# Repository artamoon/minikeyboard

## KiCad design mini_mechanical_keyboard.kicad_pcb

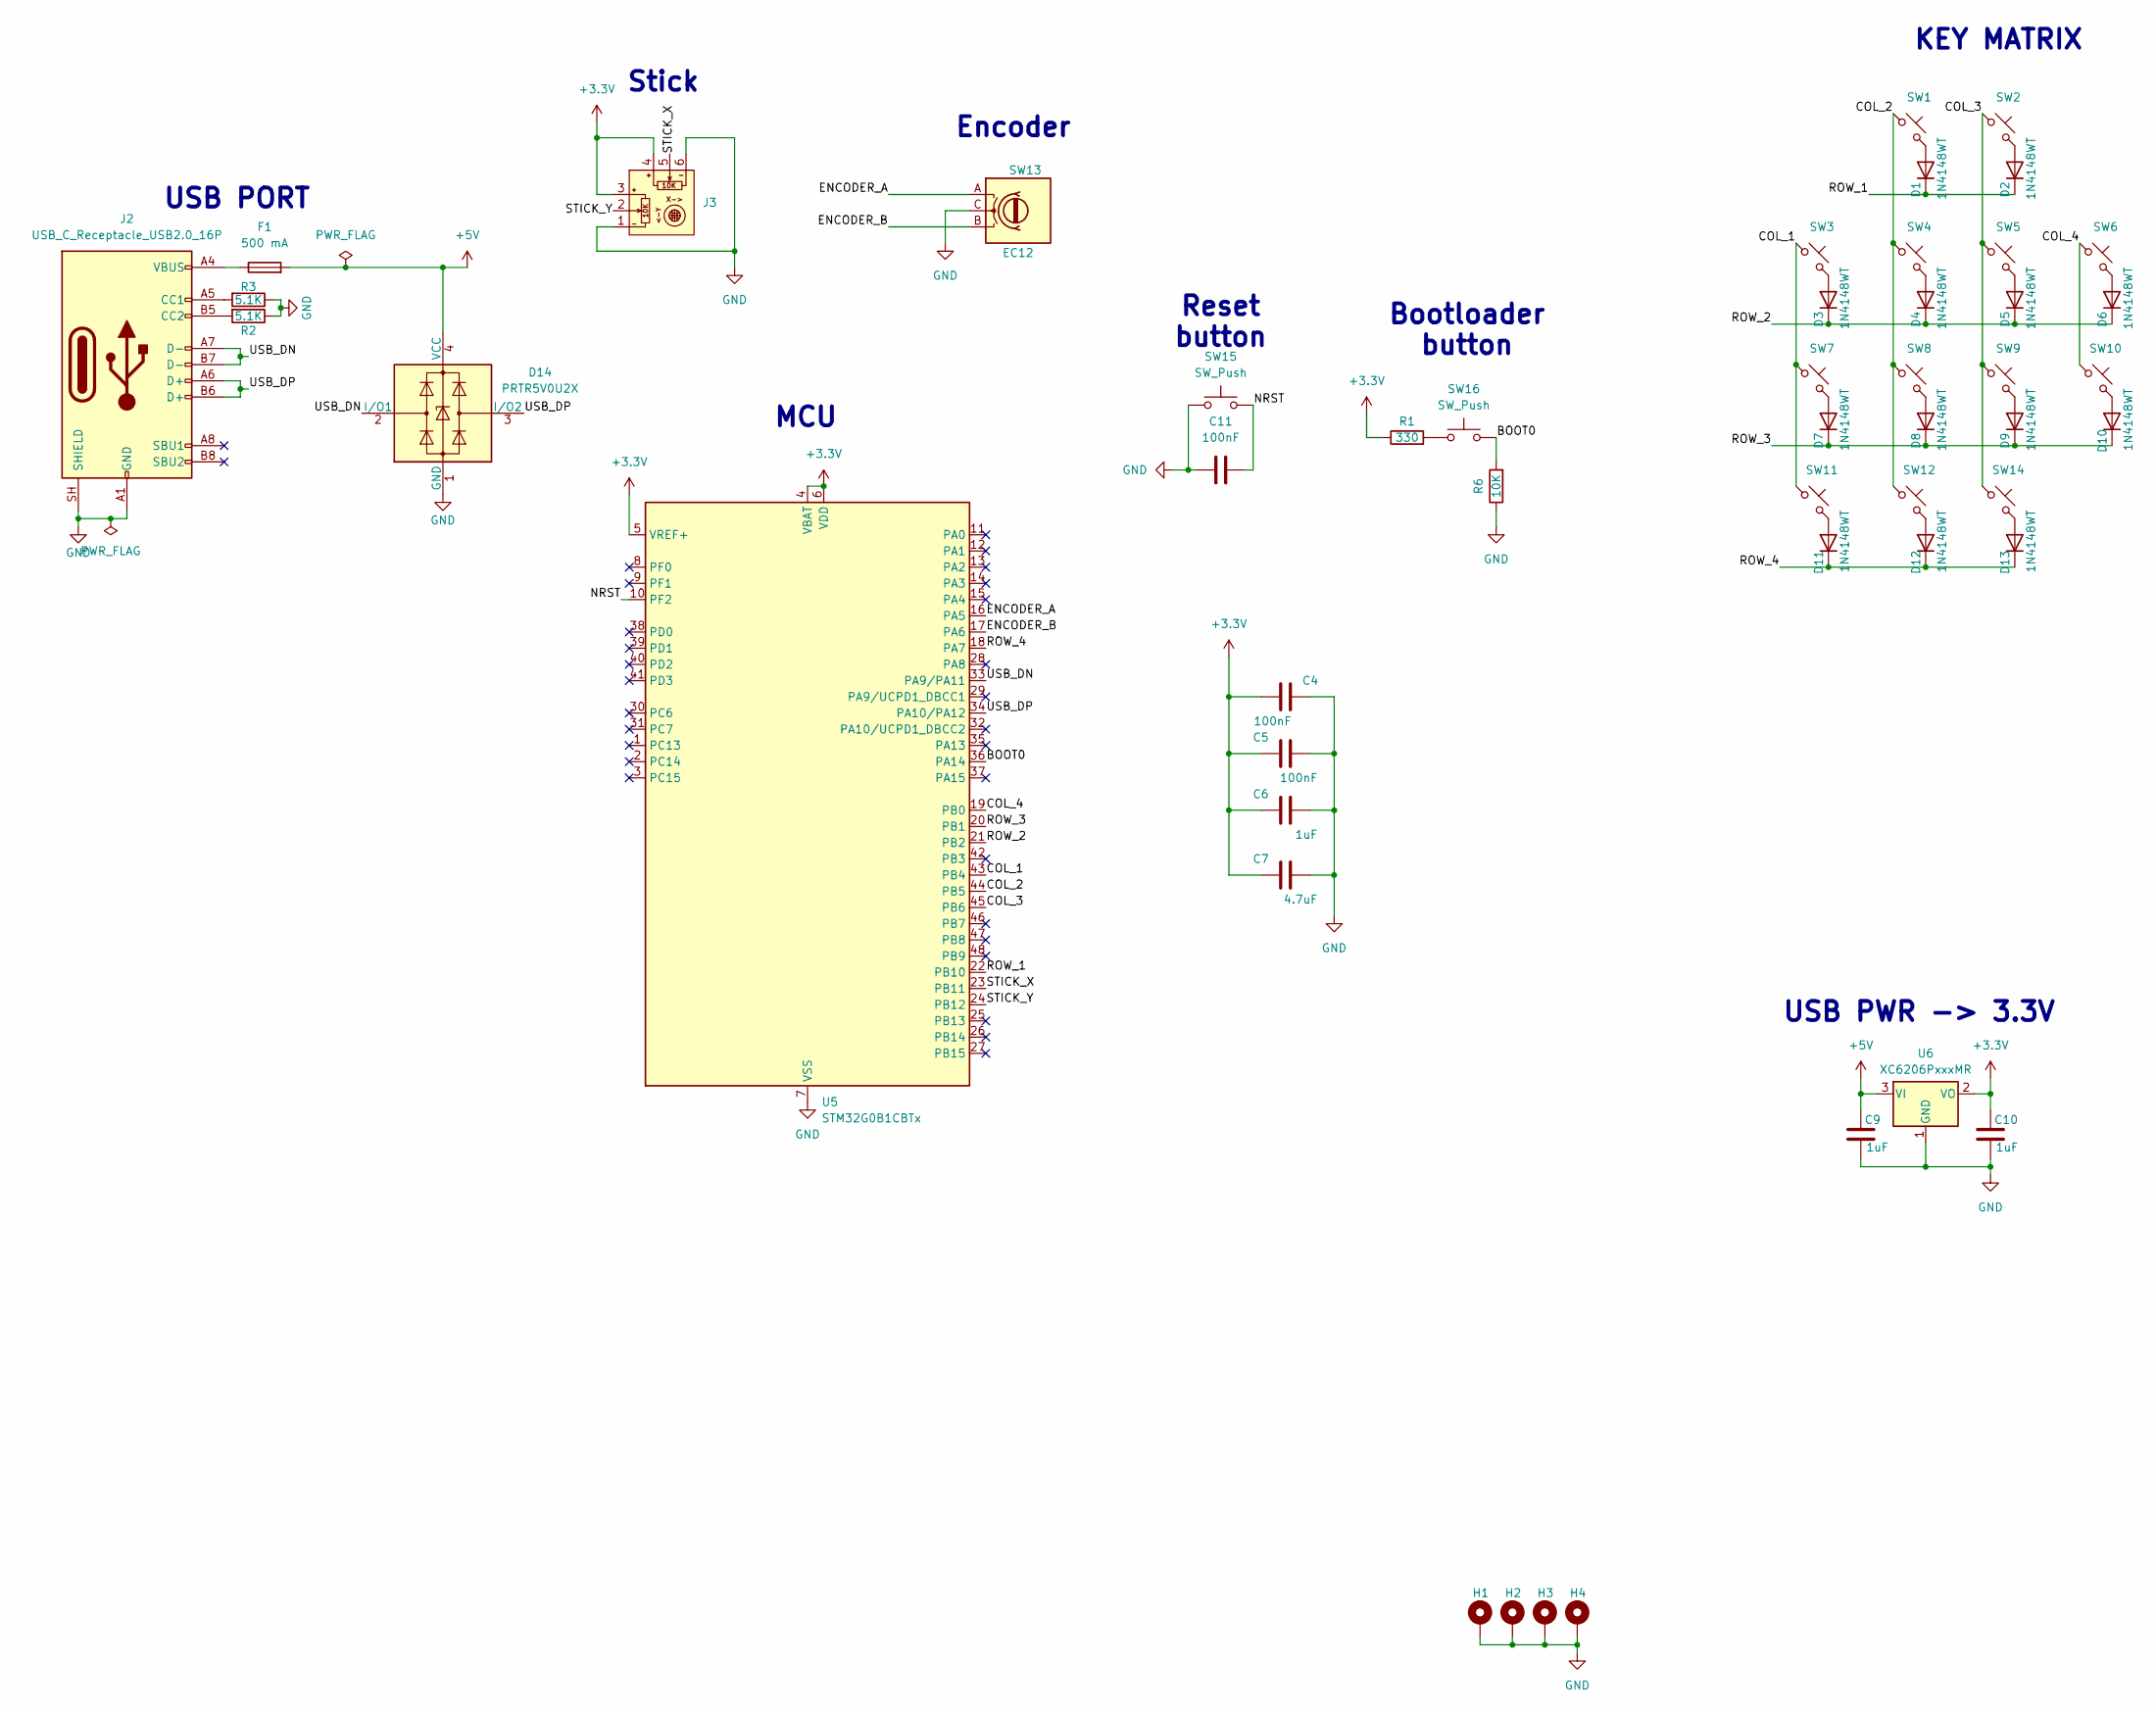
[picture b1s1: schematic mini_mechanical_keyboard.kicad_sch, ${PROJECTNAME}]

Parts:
C4, C5: 100nF; C_0402_1005Metric; LCSC C1525
C6: 1uF; C_0603_1608Metric; LCSC C1525
C7: 4.7uF; C_0805_2012Metric; LCSC C19666
C9, C10: 1uF; C_0603_1608Metric; LCSC C15525
C11: 100nF; C_0402_1005Metric
D1, D2, D3, D4, D5, D6, D7, D8, D9, D10, D11, D12, D13: 1N4148WT; D_SOD-523; LCSC C7420320
D14: PRTR5V0U2X; SOT-143
F1: 500 mA; Fuse_1206_3216Metric_Pad1.42x1.75mm_HandSolder
H1, H2, H3, H4: MountingHole_Pad; MountingHole_2.7mm_Pad_Via
J2: USB_C_Receptacle_USB2.0_16P; USB_C_HRO_TYPE-C-31-M-12
J3: Mini 2-Axis Analog Thumbstick
R1: 330; R_0402_1005Metric
R2, R3: 5.1K; R_0402_1005Metric; LCSC C25905
R6: 10K; R_0402_1005Metric
SW1, SW2, SW3, SW4, SW5, SW6, SW7, SW8, SW9, SW10, SW12, SW14: SW_Push_45deg; SW_choc_v2_HS_CPG135001S30_1u
SW11: SW_Push_45deg; SW_SPST_SKQG_WithStem
SW13: EC12; RotaryEncoder_Alps_EC12E_Vertical_H20mm
SW15, SW16: SW_Push; SW_SPST_TL3305A
U5: STM32G0B1CBTx; LQFP-48_7x7mm_P0.5mm
U6: XC6206PxxxMR; SOT-23-3

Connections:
+3.3V: C4.2, C5.1, C6.1, C7.1, C10.1, J3.3, J3.4, R1.1, U5.4 (VBAT), U5.5 (VREF+), U5.6 (VDD), U6.2 (VO)
+5V: C9.1, D14.4 (VCC), F1.2, U6.3 (VI)
/BOOT0: R6.2, SW16.2, U5.36 (PA14)
/COL_1: SW3.1, SW7.1, SW11.1, U5.43 (PB4)
/COL_2: SW1.1, SW4.1, SW8.1, SW12.1, U5.44 (PB5)
/COL_3: SW2.1, SW5.1, SW9.1, SW14.1, U5.45 (PB6)
/COL_4: SW6.1, SW10.1, U5.19 (PB0)
/ENCODER_A: SW13.A, U5.16 (PA5)
/ENCODER_B: SW13.B, U5.17 (PA6)
/NRST: C11.2, SW15.2, U5.10 (PF2)
/ROW_1: D1.1 (K), D2.1 (K), U5.22 (PB10)
/ROW_2: D3.1 (K), D4.1 (K), D5.1 (K), D6.1 (K), U5.21 (PB2)
/ROW_3: D7.1 (K), D8.1 (K), D9.1 (K), D10.1 (K), U5.20 (PB1)
/ROW_4: D11.1 (K), D12.1 (K), D13.1 (K), U5.18 (PA7)
/STICK_X: J3.5, U5.23 (PB11)
/STICK_Y: J3.2, U5.24 (PB12)
/USB_DN: D14.2 (I/O1), J2.A7 (D-), J2.B7 (D-), U5.33 (PA9/PA11)
/USB_DP: D14.3 (I/O2), J2.A6 (D+), J2.B6 (D+), U5.34 (PA10/PA12)
GND: C4.1, C5.2, C6.2, C7.2, C9.2, C10.2, C11.1, D14.1 (GND), H1.1 (1_1), H2.1 (1_1), H3.1 (1_1), H4.1 (1_1), J2.A1 (GND), J2.A12 (GND), J2.B1 (GND), J2.B12 (GND), J2.SH (SHIELD), J3.1, J3.6, R2.1, R3.1, R6.1, SW13.C, SW15.1, U5.7 (VSS), U6.1 (GND)
unnamed: D1.2 (A), SW1.2
unnamed: D2.2 (A), SW2.2
unnamed: D3.2 (A), SW3.2
unnamed: D4.2 (A), SW4.2
unnamed: D5.2 (A), SW5.2
unnamed: D6.2 (A), SW6.2
unnamed: D7.2 (A), SW7.2
unnamed: D8.2 (A), SW8.2
unnamed: D9.2 (A), SW9.2
unnamed: D10.2 (A), SW10.2
unnamed: D11.2 (A), SW11.2
unnamed: D12.2 (A), SW12.2
unnamed: D13.2 (A), SW14.2
unnamed: F1.1, J2.A4 (VBUS), J2.A9 (VBUS), J2.B4 (VBUS), J2.B9 (VBUS)
unnamed: J2.A5 (CC1), R3.2
unnamed: J2.B5 (CC2), R2.2
unnamed: R1.2, SW16.1

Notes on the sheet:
Encoder
USB PORT
Bootloader button
MCU
Reset button
KEY MATRIX
USB PWR -> 3.3V
Stick

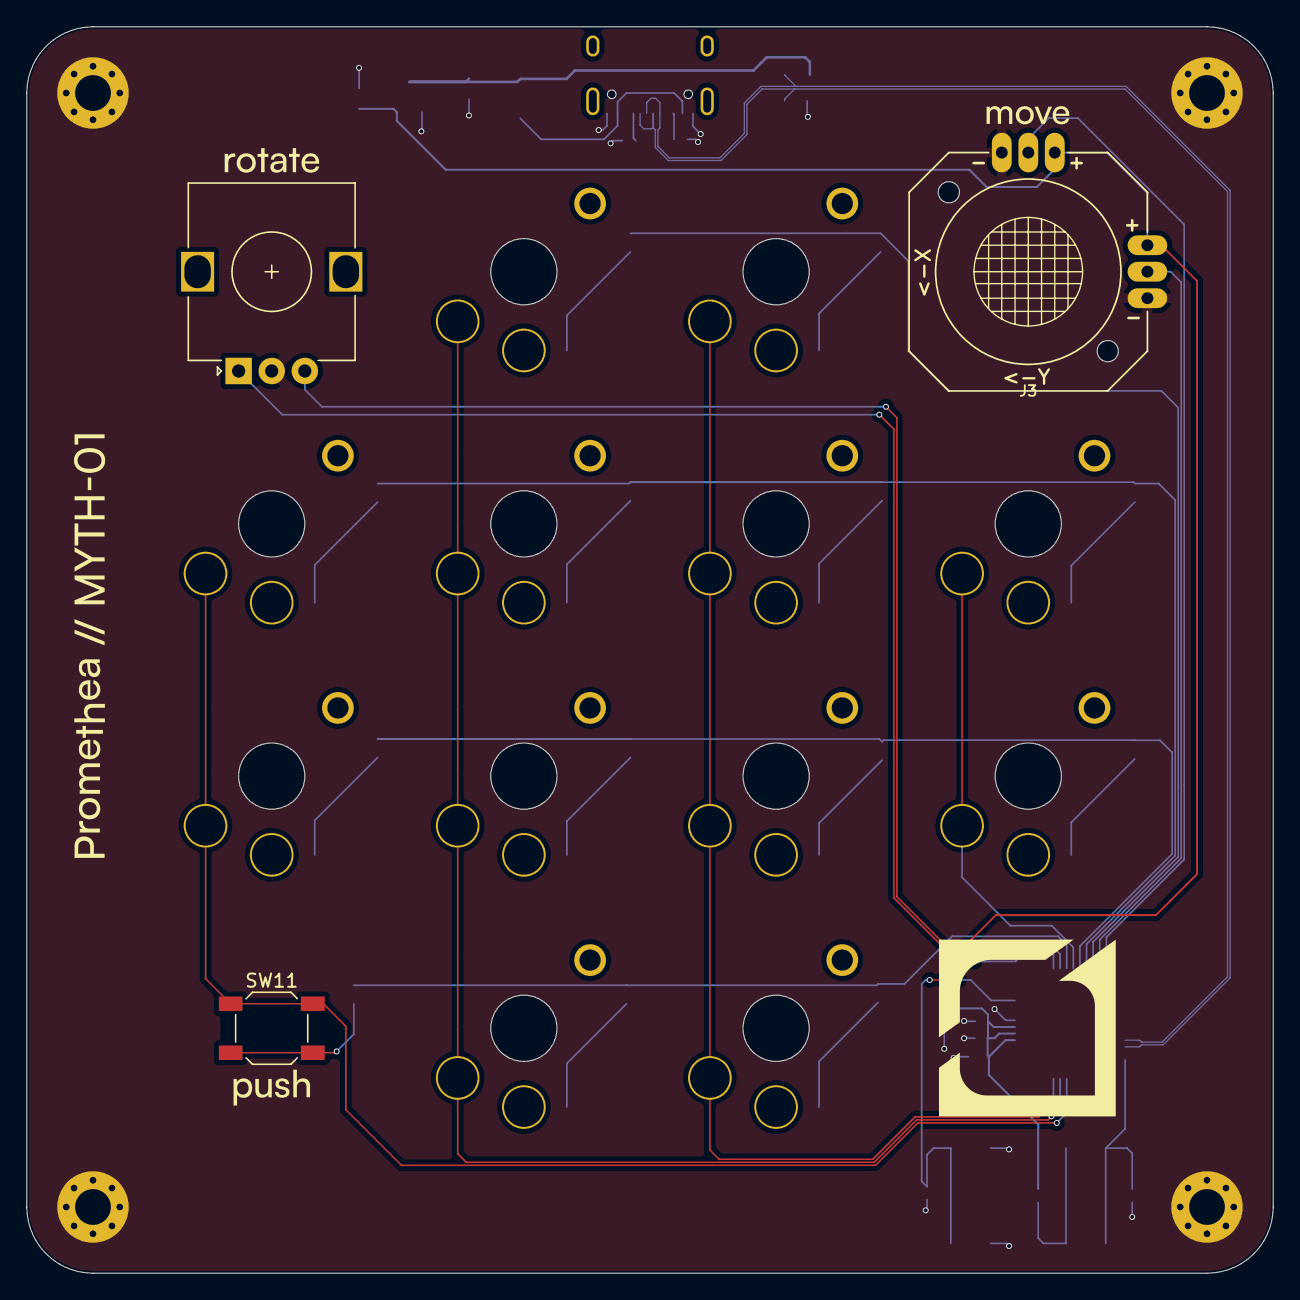
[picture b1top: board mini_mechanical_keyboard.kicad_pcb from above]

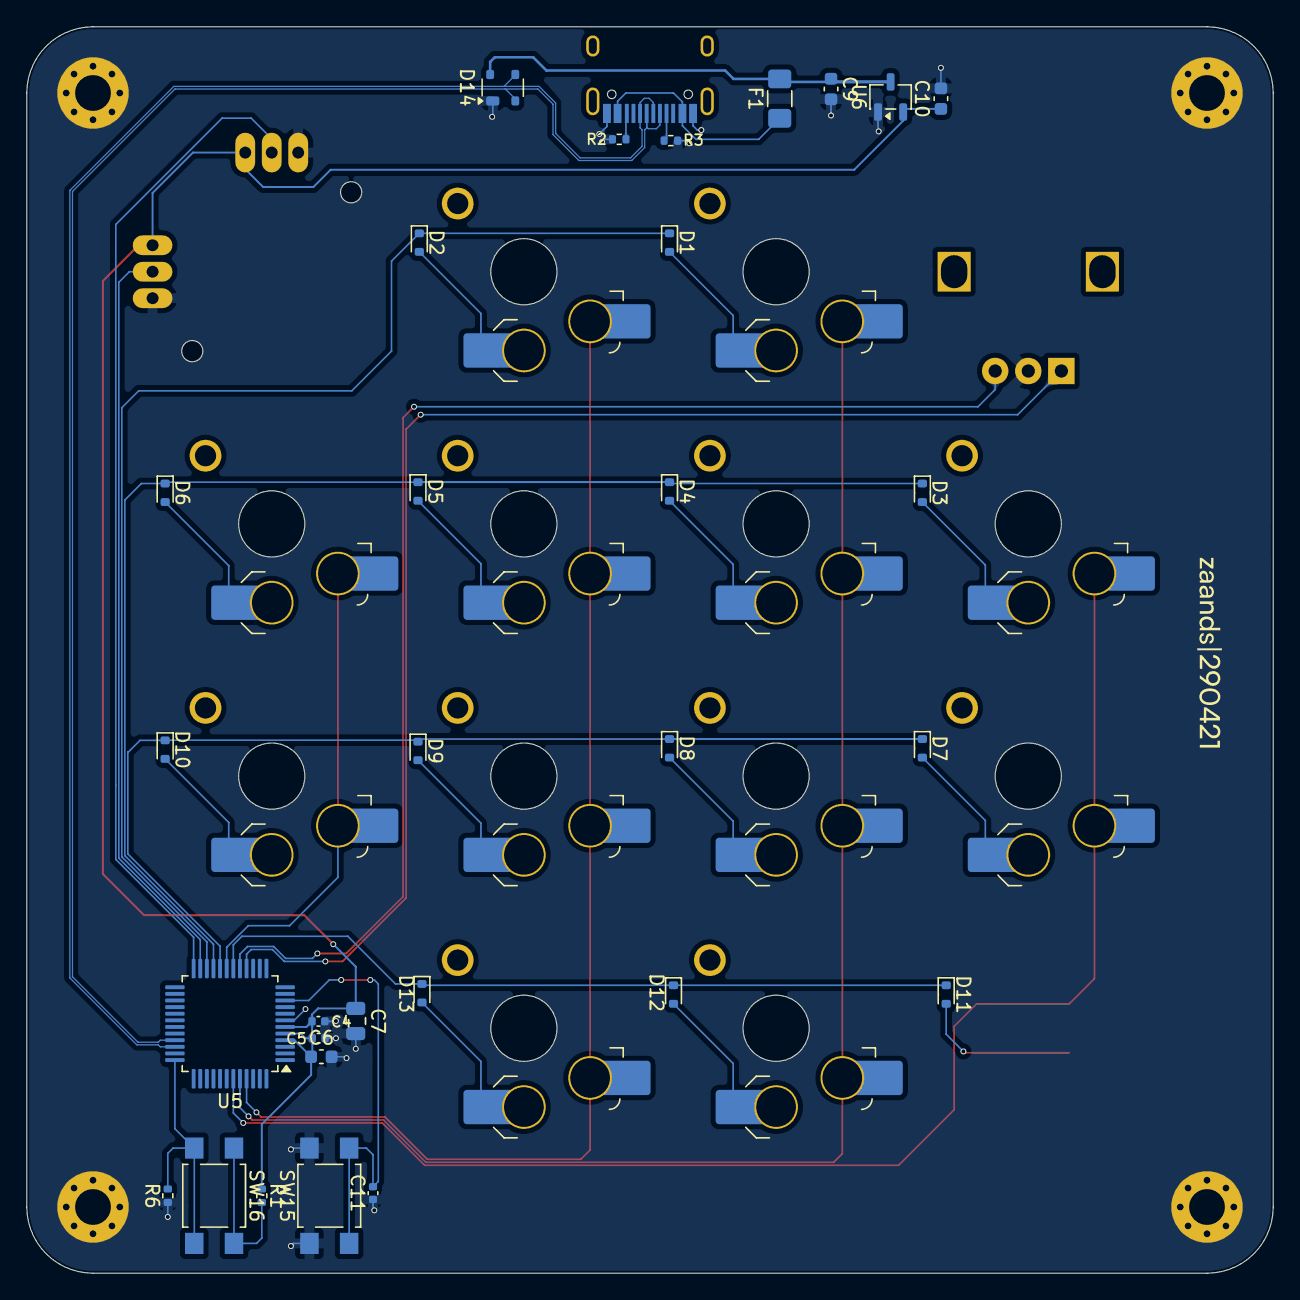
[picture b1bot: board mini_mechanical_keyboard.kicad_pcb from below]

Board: 2 copper layers, 94.2 x 94.2 mm, 50 parts (43 on the bottom side), 36 nets.

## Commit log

2026-05-20 abruz
2026-05-22 arbuz
